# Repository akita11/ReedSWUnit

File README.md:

# ReedSW Unit

磁石を近づけるとONになるリードスイッチのUnitです。ネオジム磁石のような強い磁石であれば5mm程度近づけるだけでONになります。ONになるとLEDが点灯します。UIFlowなどからは、M5Stackの[ボタンUnit](https://www.switch-science.com/products/4047)と同じように扱うことができます。

※OFF時にLEDがうっすらと点灯しますが、異常ではありません（LEDに流れている電流は20uA程度ですが高輝度LEDのためうっすらと点灯しているように見えます）

## ピン配置

Grove端子の1番から順に「SW（負論理）」「無接続」「VDD(5V/3.3V)」「GND」の順です。

## Author

Junichi Akita (akita@ifdl.jp, @akita11)

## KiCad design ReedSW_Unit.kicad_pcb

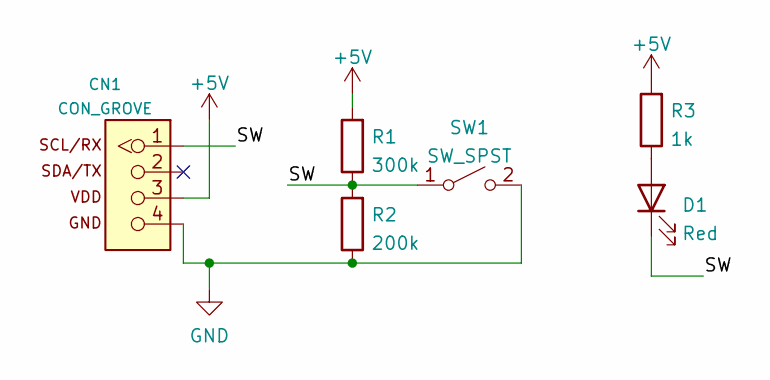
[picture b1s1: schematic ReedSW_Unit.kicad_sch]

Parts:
CN1: CON_GROVE; CON_GROVE_H
D1: Red; LED_0603_1608Metric
R1: 300k; R_0603_1608Metric
R2: 200k; R_0603_1608Metric
R3: 1k; R_0603_1608Metric
SW1: SW_SPST; SW_LeadSW_SP3-1A16

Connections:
+5V: CN1.3, R1.2, R3.2
/SW: CN1.1, D1.1 (K), R1.1, R2.2, SW1.1 (A)
GND: CN1.4, R2.1, SW1.2 (B)
unnamed: D1.2 (A), R3.1

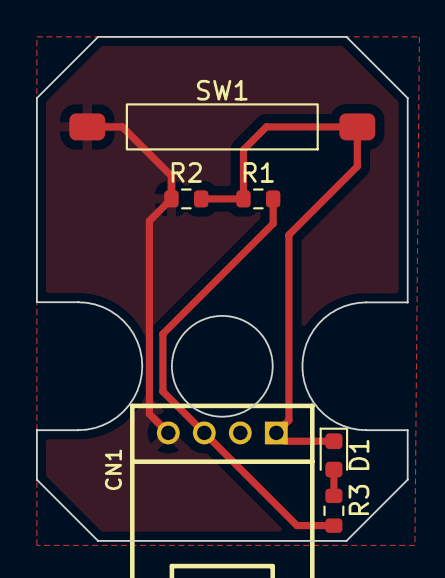
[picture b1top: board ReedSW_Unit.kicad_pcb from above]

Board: 2 copper layers, 20.6 x 28.0 mm, 6 parts (0 on the bottom side), 4 nets.

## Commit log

2024-03-31 add case-version photo
